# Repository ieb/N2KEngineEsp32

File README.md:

# NMEA 2000 Marine Diesel Engine Interface (ESP32-C3)

This project provides an open, high-reliability NMEA 2000 marine engine interface for diesel propulsion engines. Built on the **ESP32-C3** microcontroller and **ADS1115 16-bit ADCs**, it monitors engine speed, operating pressures, temperatures, electrical systems, and alarm conditions, broadcasting them across the vessel's NMEA 2000 CAN network.

---

## High-Level Architecture

```
                    +------------------------------------+
                    |             ESP32-C3               |
                    |                                    |
Flywheel Sensor --->| GPIO4 (Pulse Interrupt)            |
Stop Relay      --->| GPIO5 (Coil Sense)                 |
Glow Relay      --->| GPIO6 (Coil Sense)                 |
Start Relay     --->| GPIO7 (Coil Sense)                 |
1-Wire DS18B20  --->| GPIO0 (Dallas Temp Bus)            |
                    |                                    |
I2C Bus (SDA/SCL) ->| GPIO8 / GPIO9                      |
                    +-----+------------------------+-----+
                          |                        |
                          v                        v
             +-------------------------+     +------------+
             | 3x ADS1115 16-bit ADCs  |     | CAN / TWAI | (GPIO3 TX, GPIO1 RX)
             | (Running at 5V via LS)  |     +-----+------+
             +------------+------------+           |
                          |                        v
                          |                 +--------------+
  NTC1: Exhaust Water Trap|                 |  NMEA 2000   |
  NTC2: Alternator Temp   |                 |     Bus      |
  NTC3: Engine Room Temp  |                 +--------------+
  NTC4: Gearbox Temp      |
  NTC5: Exhaust Elbow Temp|
  Oil Pressure (0-5V)     |
  Coolant Sensor (12V)    |
  Engine Block Offset     |
  Engine Battery Voltage  |
  Alternator B+ Voltage   |
  Fuel Sender (0-190 ohm) |
```

---

## Key Hardware Peripherals & Pinout

| Pin | Peripheral | Purpose |
| :--- | :--- | :--- |
| **GPIO0** | 1-Wire | Dallas DS18B20 digital temperature bus (4K7 pull-up to 3V3) |
| **GPIO1** | CAN-RX | ESP32 TWAI CAN bus receive |
| **GPIO3** | CAN-TX | ESP32 TWAI CAN bus transmit |
| **GPIO2** | Bench Output | Optional LEDC test signal for RPM bench testing (CLI `T`) |
| **GPIO4** | Pulse Input | Flywheel reactive pickup via LM393 comparator (30 teeth per revolution) |
| **GPIO5** | Digital Input | Stop Relay Coil (10k / 4.7k divider from 12V, BAT46 clamp to 3V3) |
| **GPIO6** | Digital Input | Glow Plug Relay Coil (10k / 4.7k divider from 12V, BAT46 clamp to 3V3) |
| **GPIO7** | Digital Input | Start Relay Coil (10k / 4.7k divider from 12V, BAT46 clamp to 3V3) |
| **GPIO8** | I2C SDA | 400 kHz I2C data to 3x ADS1115 ADCs |
| **GPIO9** | I2C SCL | 400 kHz I2C clock to 3x ADS1115 ADCs |

### ADC Mapping (3x ADS1115 @ 5V, 64 SPS)
* **ADC1 (`0x48`, Addr $\to$ GND)**:
  * `AIN0`: NTC1 (10K NTC, 5V 4k7 pullup) — Exhaust Water Trap
  * `AIN1`: NTC2 (10K NTC, 5V 4k7 pullup) — Alternator Temperature
  * `AIN2`: NTC3 (10K NTC, 5V 4k7 pullup) — Engine Room Air Temperature
  * `AIN3`: Alternator Voltage Divider (10k / 4.7k)
* **ADC2 (`0x49`, Addr $\to$ VDD)**:
  * `AIN0`: Oil Pressure Sender (0–5V sensor)
  * `AIN1`: Engine Coolant Sensor (12V 1k pullup)
  * `AIN2`: Engine Block Negative Offset Divider (5V — 10k — ADC — 10k — Engine Block -)
  * `AIN3`: Engine Starting Battery Voltage Divider (10k / 4.7k)
* **ADC3 (`0x4B`, Addr $\to$ SCL)**:
  * `AIN0`: NTC4 (10K NTC, 5V 4k7 pullup) — Gearbox Temperature
  * `AIN1`: NTC5 (10K NTC, 5V 4k7 pullup) — Exhaust Elbow Temperature
  * `AIN2`: Fuel Tank Level Sender (European 0–190 $\Omega$, 5V 1k pullup)
  * `AIN3`: Spare Voltage Divider (10k / 4.7k)

---

## Signal Processing & Calibrations

1. **Engine Speed (RPM)**:
   * Computed from flywheel pulses: $\text{RPM} = \text{Hz} \times 2.0$.
   * Two implementations, selected with `RPM_SENSOR_EDGE_TIMING` in `src/config.h`:
     * **Edge timing** (`EdgeRpmSensor`, default): the ISR timestamps edges (1 µs) and RPM is computed over whole revolutions, giving a new value every revolution with accuracy limited only by interrupt latency jitter (~0.01–0.04%). Registered as an IRAM interrupt so pulses are not lost during flash writes; edges closer than 150 µs are rejected as glitches.
     * **Window counting** (`RpmSensor`): counts pulses over a ~100 ms window; ±1 pulse (±20 RPM) quantisation plus `millis()` jitter.
   * The ESP32-C3 has no PCNT (pulse counter) peripheral, so hardware counting is not available on this board.
   * The native tests print a side-by-side comparison of both implementations; on the board use the `T` bench signal.
   * Details, measurements and caveats: [docs/rpm_measurement.md](docs/rpm_measurement.md).
   * Engine is considered **Running** when $\text{RPM} \ge 800$ and **Stopping** when $\text{RPM} < 500$.
2. **10K NTC Thermistors (NTC1–NTC5)**:
   * Converted analytically using the exact Beta parameter model ($\frac{1}{T} = \frac{1}{T_0} + \frac{1}{\beta} \ln\left(\frac{R}{R_0}\right)$ with $R_0 = 10000\,\Omega$, $T_0 = 298.15\text{ K}$, $\beta = 3950\text{ K}$, $R_{\text{top}} = 4700\,\Omega$).
   * Provides smooth, continuous sub-0.01°C resolution matching the 16-bit ADS1115 without piecewise discretization or boundary kinks.
3. **Engine Block Negative Offset Compensation**:
   * Measures voltage drop between boat DC ground and engine block negative caused by heavy alternator charging current:
     $$V_{block} = 2.0 \cdot V_{adc} - 5.0\text{ V}$$
   * The Volvo Penta coolant sensor is connected to the engine block; its voltage reading and supply rail are automatically adjusted relative to $V_{block}$ to prevent false temperature spikes during high charging.
4. **Volvo Penta Coolant Temperature Sender**:
   * Evaluated through a dedicated lookup table (`coolantTable`, 10°C to 120°C) with ratiometric battery supply voltage compensation.
5. **Oil Pressure Sensor**:
   * Linear 0.5V (0 psi) to 4.5V (100 psi) transfer function with disconnection detection.
6. **Fuel Tank Level**:
   * Supports European 0–190 $\Omega$ resistive senders (0 $\Omega$ = Empty, 190 $\Omega$ = Full), scaled to 0.0%–100.0%.

---

## Alarms & Raw Water Flow Collapse Protection

* **15-Second Startup Grace Period**: Prevents spurious alarms while the engine spins up to idle.
* **Raw Water Flow Collapse Protection (Exhaust Elbow NTC5)**:
  * Evaluates rate-of-rise over a 30-second sliding anchor window. If exhaust elbow temperature climbs $\ge +8.0\text{°C}$ inside 30 seconds once above 35°C baseline, a raw water flow failure alarm is tripped immediately.
  * Absolute over-temperature alarm at $> 45.0\text{°C}$. If sustained for $> 5$ seconds, triggers an **Emergency Stop** discrete alarm.
* **Engine Protection Alarms**:
  * Coolant Over-Temperature: $> 97.0\text{°C}$ sustained $> 15$ seconds.
  * Low Oil Pressure: $< 10.0\text{ PSI}$ (68.9 kPa) sustained $> 5$ seconds while running.
  * Low System Voltage: Engine battery $< 11.8\text{ V}$ sustained $> 5$ seconds.
  * Alternator Charge Indicator: Alternator voltage $< 12.2\text{ V}$ sustained $> 5$ seconds.
  * High Alternator Temperature: Warning Level 1 triggered at $> 110.0\text{°C}$.
  * High Engine Room Temperature: Warning Level 1 triggered at $> 70.0\text{°C}$.

---

## Non-Volatile Storage & Event Logging

The flash memory uses a **2MB Application / 2MB SPIFFS** partition layout (`src/no_ota.csv`):
* **Engine Hours Accumulator**: Accumulated per second while $\text{RPM} \ge 800$, committed to wear-leveled NVS Preferences.
* **Persistent Event History**: Historical alarms are appended to `/events.csv` on the SPIFFS filesystem.
* **No flash writes while the engine runs**: flash writes stall non-IRAM interrupts (CAN today, BLE later) for up to tens of ms during a sector erase. While running, engine hours and alarm events are held in RTC no-init memory (survives crashes, watchdog resets and restarts) and written to flash when the stop relay is energised, when the engine stops and before a CLI restart. A valid RTC copy that is ahead of flash is recovered at boot. A backstop save of engine hours every `ENGINE_HOURS_BACKSTOP_SAVE_S` (default 3600 s, 0 disables) protects against an abnormal power cut; board power normally stays on 30–60 s after shutdown. Alarm flags are still sent immediately in PGN 127489. Setting hours (`E`) and clearing events (`C` / N2K command) write immediately.
* **GPS UTC Synchronization**: Automatically synchronizes timestamps when NMEA 2000 System Time (**PGN 126992**) is received from on-bus GPS receivers.

---

## NMEA 2000 Messages & Display Remapping

To allow standard marine multifunction displays (MFDs) and dedicated instruments (such as Raymarine i70) to present all engine and electrical metrics without proprietary software:

| PGN | Name | Period | Special Mapping / Rationale |
| :--- | :--- | :--- | :--- |
| **127488** | Engine Parameters, Rapid Update | 500 ms | RPM broadcast when engine is running ($\text{RPM} \ge 800$). |
| **127489** | Engine Parameters, Dynamic | 1000 ms | **Alternator Temp (NTC2)** sent as `Engine Oil Temperature` so standard gauges display alternator thermal load. Also conveys coolant temp, alternator voltage, total engine hours, oil pressure, and discrete alarm bitfields. |
| **127493** | Transmission Parameters, Dynamic | 4.85 s | **Exhaust Water Trap (NTC1)** sent as `Transmission Oil Temperature` for displays lacking an exhaust gauge. |
| **127508** | Battery Status | 1.0 s | Broadcasts two instances:<br>• **Instance 0**: Engine Starting Battery Voltage.<br>• **Instance 2**: Alternator Output Voltage & Operating Temperature. |
| **127505** | Fluid Level | 2.5 s | Tank Instance 0, Fuel level % (60.0 L capacity default). |
| **130312** | Temperature (Legacy) | 4.85 s | Emits Exhaust Gas (Source 14), Engine Room (Source 3), Alternator (Source 30), and Dallas 1-Wire sensors (Source 31+i). |
| **130316** | Extended Temperature | 2.5 s | Emits high-resolution (0.001 K) temperatures. |

---

## Interactive Serial Console

Connect to the USB Serial port at **115200 baud** for real-time monitoring and commands:

* `h` — Show command menu
* `s` — Print complete formatted engine status dashboard
* `F` — Toggle Fake 1000 RPM mode for bench testing
* `E` — Set / calibrate accumulated engine hours
* `l` — Dump SPIFFS alarm event log
* `C` — Clear SPIFFS event history
* `d` — Toggle raw ADC voltage debug stream
* `T` — Cycle the RPM bench test signal on GPIO2 (off → 100 Hz → 400 Hz → 1500 Hz) and print min/mean/max/std-dev of the measured RPM every 2 s. Wire GPIO2 → 1K → GPIO4 and short the flywheel input (J15) so the LM393 output is released. Build once with each `RPM_SENSOR_EDGE_TIMING` setting to compare.
* `R` — Software restart of the ESP32-C3

---

## Building & Flashing

This project uses [PlatformIO](https://platformio.org/):

```bash
# Build firmware
pio run

# Flash to ESP32-C3
pio run -t upload

# Open Serial Monitor
pio device monitor
```

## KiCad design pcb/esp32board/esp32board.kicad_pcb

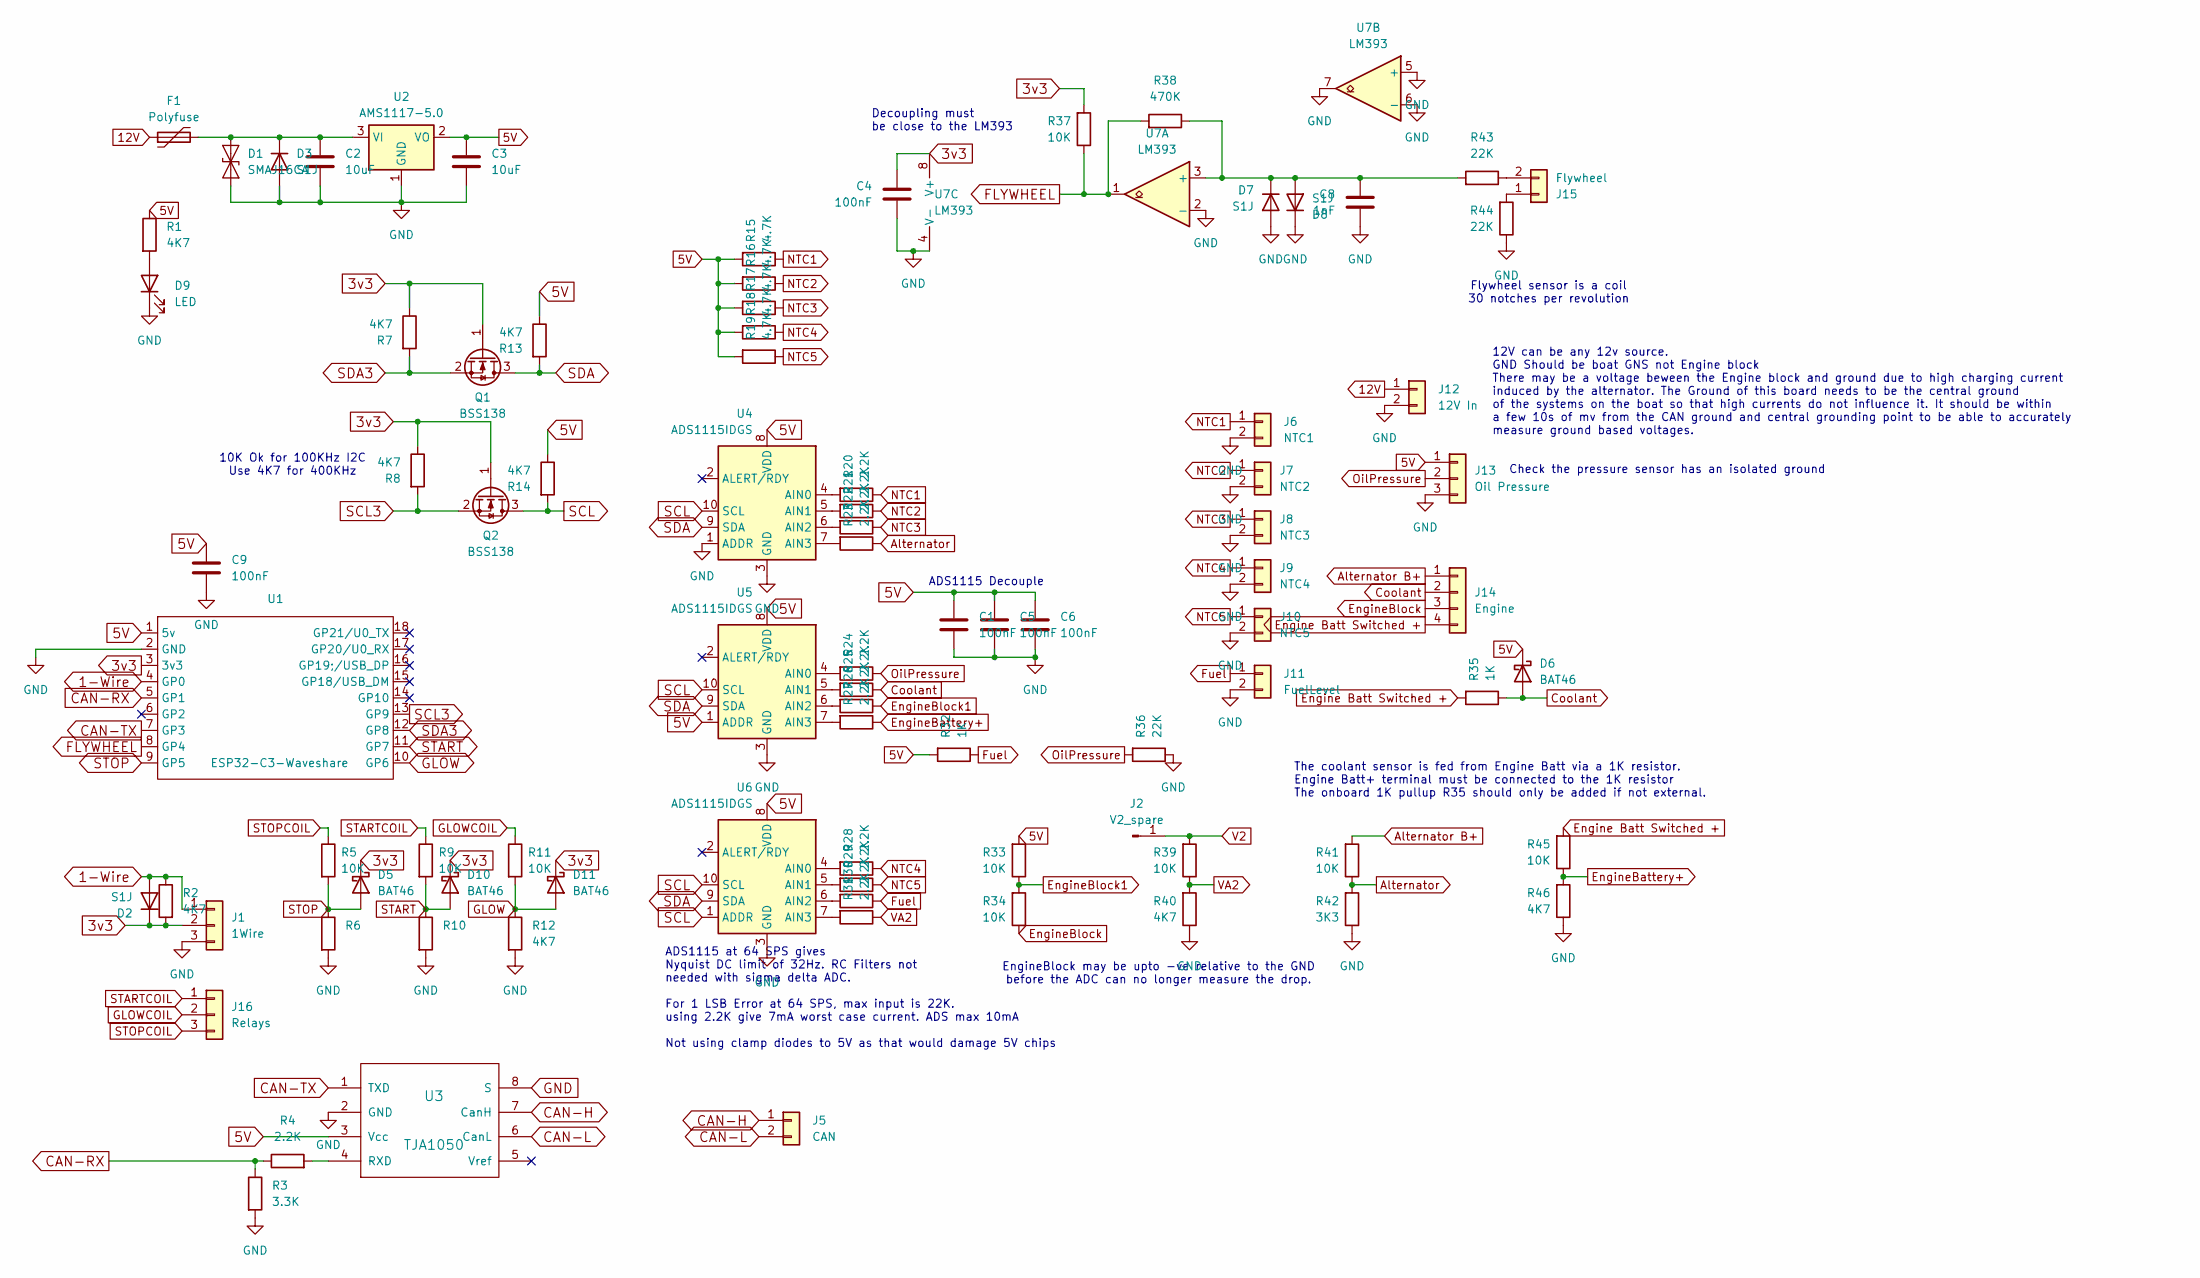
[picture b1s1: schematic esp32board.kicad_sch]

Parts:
C1, C4, C5, C6, C9: 100nF; C_0805_2012Metric_Pad1.18x1.45mm_HandSolder
C2, C3: 10uF; C_1206_3216Metric_Pad1.33x1.80mm_HandSolder
C8: 1nF; C_0805_2012Metric_Pad1.18x1.45mm_HandSolder
D1: SMAJ16CA; D_SMA-SMB_Universal_Handsoldering
D2, D3, D7, D8: S1J; D_SMA
D5, D6, D10, D11: BAT46; D_SOD-123
D9: LED; LED_0805_2012Metric_Pad1.15x1.40mm_HandSolder
F1: Polyfuse; Fuse_1812_4532Metric_Pad1.30x3.40mm_HandSolder
J1: 1Wire; JST_XH_B3B-XH-A_1x03_P2.50mm_Vertical
J2: V2_spare; PinHeader_1x01_P2.54mm_Vertical
J5: CAN; TerminalBlock_Phoenix_MKDS-1,5-2-5.08_1x02_P5.08mm_Horizont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
J6: NTC1; JST_XH_B2B-XH-A_1x02_P2.50mm_Vertical
J7: NTC2; JST_XH_B2B-XH-A_1x02_P2.50mm_Vertical
J8: NTC3; JST_XH_B2B-XH-A_1x02_P2.50mm_Vertical
J9: NTC4; JST_XH_B2B-XH-A_1x02_P2.50mm_Vertical
J10: NTC5; JST_XH_B2B-XH-A_1x02_P2.50mm_Vertical
J11: FuelLevel; JST_XH_B2B-XH-A_1x02_P2.50mm_Vertical
J12: 12V In; JST_XH_B2B-XH-A_1x02_P2.50mm_Vertical
J13: Oil Pressure; JST_XH_B3B-XH-A_1x03_P2.50mm_Vertical
J14: Engine; JST_XH_B4B-XH-A_1x04_P2.50mm_Vertical
J15: Flywheel; JST_XH_B2B-XH-A_1x02_P2.50mm_Vertical
J16: Relays; JST_XH_B3B-XH-A_1x03_P2.50mm_Vertical
Q1, Q2: BSS138; SOT-23
R1, R2, R6, R7, R8, R10, R12, R13, R14, R40, R46: 4K7; R_0805_2012Metric_Pad1.20x1.40mm_HandSolder
R3: 3.3K; R_0805_2012Metric_Pad1.20x1.40mm_HandSolder
R4, R20, R21, R22, R23, R24, R25, R26, R27, R28, R29, R30, R31: 2.2K; R_0805_2012Metric_Pad1.20x1.40mm_HandSolder
R5, R9, R11, R33, R34, R37, R39, R41, R45: 10K; R_0805_2012Metric_Pad1.20x1.40mm_HandSolder
R15, R16, R17, R18, R19: 4.7K; R_0805_2012Metric_Pad1.20x1.40mm_HandSolder
R32: 1K; R_0805_2012Metric_Pad1.20x1.40mm_HandSolder
R35: 1K; R_Axial_DIN0204_L3.6mm_D1.6mm_P5.08mm_Horizontal
R36, R43, R44: 22K; R_0805_2012Metric_Pad1.20x1.40mm_HandSolder
R38: 470K; R_0805_2012Metric_Pad1.20x1.40mm_HandSolder
R42: 3K3; R_0805_2012Metric_Pad1.20x1.40mm_HandSolder
U1: ESP32-C3-Waveshare; ESP-C3-Zero-Waveshare
U2: AMS1117-5.0; SOT-223-3_TabPin2
U3: TJA1050; SOIC-8_3.9x4.9mm_P1.27mm
U4, U5, U6: ADS1115IDGS; TSSOP-10_3x3mm_P0.5mm
U7: LM393; SOIC-8_3.9x4.9mm_P1.27mm

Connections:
1-Wire: D2.2 (A), J1.1, R2.1, U1.4 (GP0)
3v3: C4.2, D2.1 (K), D5.1 (K), D10.1 (K), D11.1 (K), J1.2, Q1.1 (G), Q2.1 (G), R2.2, R7.1, R8.1, R37.2, U1.3 (3v3), U7.8 (V+)
5V: C1.1, C3.1, C5.1, C6.1, C9.1, D6.1 (K), J13.1, R1.1, R13.1, R14.1, R15.2, R16.2, R17.2, R18.2, R19.2, R32.2, R33.2, U1.1 (5v), U2.2 (VO), U3.3 (Vcc), U4.8 (VDD), U5.1 (ADDR), U5.8 (VDD), U6.8 (VDD)
12V: F1.1, J12.1
Alternator: R23.1, R41.1, R42.2
Alternator B+: J14.1, R41.2
CAN-H: J5.1, U3.7 (CanH)
CAN-L: J5.2, U3.6 (CanL)
CAN-RX: R3.1, R4.1, U1.5 (GP1)
CAN-TX: U1.7 (GP3), U3.1 (TXD)
Coolant: D6.2 (A), J14.2, R25.1, R35.1
Engine Batt Switched +: J14.4, R35.2, R45.2
EngineBattery+: R27.1, R45.1, R46.2
EngineBlock: J14.3, R34.1
EngineBlock1: R26.1, R33.1, R34.2
FLYWHEEL: R37.1, R38.2, U1.8 (GP4), U7.1
Fuel: J11.1, R30.1, R32.1
GLOW: D11.2 (A), R11.2, R12.1, U1.10 (GP6)
GLOWCOIL: J16.2, R11.1
GND: C1.2, C2.2, C3.2, C4.1, C5.2, C6.2, C8.1, C9.2, D1.1 (A1), D3.2 (A), D7.2 (A), D8.1 (K), D9.1 (K), J1.3, J6.2, J7.2, J8.2, J9.2, J10.2, J11.2, J12.2, J13.3, R3.2, R6.2, R10.2, R12.2, R36.1, R40.1, R42.1, R44.1, R46.1, U1.2 (GND), U2.1 (GND), U3.2 (GND), U3.8 (S), U4.1 (ADDR), U4.3 (GND), U5.3 (GND), U6.3 (GND), U7.2 (-), U7.4 (V-), U7.5 (+), U7.6 (-), U7.7
NTC1: J6.1, R15.1, R20.1
NTC2: J7.1, R16.1, R21.1
NTC3: J8.1, R17.1, R22.1
NTC4: J9.1, R18.1, R28.1
NTC5: J10.1, R19.1, R29.1
unnamed: C2.1, D1.2 (A2), D3.1 (K), F1.2, U2.3 (VI)
unnamed: C8.2, D7.1 (K), D8.2 (A), R38.1, R43.2, U7.3 (+)
unnamed: D9.2 (A), R1.2
unnamed: J15.1, R44.2
unnamed: J15.2, R43.1
unnamed: R4.2, U3.4 (RXD)
unnamed: R20.2, U4.4 (AIN0)
unnamed: R21.2, U4.5 (AIN1)
unnamed: R22.2, U4.6 (AIN2)
unnamed: R23.2, U4.7 (AIN3)
unnamed: R24.2, U5.4 (AIN0)
unnamed: R25.2, U5.5 (AIN1)
unnamed: R26.2, U5.6 (AIN2)
unnamed: R27.2, U5.7 (AIN3)
unnamed: R28.2, U6.4 (AIN0)
unnamed: R29.2, U6.5 (AIN1)
unnamed: R30.2, U6.6 (AIN2)
unnamed: R31.2, U6.7 (AIN3)
OilPressure: J13.2, R24.1, R36.2
SCL: Q2.3 (D), R14.2, U4.10 (SCL), U5.10 (SCL), U6.1 (ADDR), U6.10 (SCL)
SCL3: Q2.2 (S), R8.2, U1.13 (GP9)
SDA: Q1.3 (D), R13.2, U4.9 (SDA), U5.9 (SDA), U6.9 (SDA)
SDA3: Q1.2 (S), R7.2, U1.12 (GP8)
START: D10.2 (A), R9.2, R10.1, U1.11 (GP7)
STARTCOIL: J16.1, R9.1
STOP: D5.2 (A), R5.2, R6.1, U1.9 (GP5)
STOPCOIL: J16.3, R5.1
V2: J2.1, R39.2
VA2: R31.1, R39.1, R40.2

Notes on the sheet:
ADS1115 at 64 SPS gives Nyquist DC limit of 32Hz. RC Filters not needed with sigma delta ADC. For 1 LSB Error at 64 SPS, max input is 22K. using 2.2K give 7mA worst case current. ADS max 10mA Not using clamp diodes to 5V as that would damage 5V chips
ADS1115 Decouple
Flywheel sensor is a coil 30 notches per revolution
Decoupling must be close to the LM393
EngineBlock may be upto -ve relative to the GND before the ADC can no longer measure the drop.
10K Ok for 100KHz I2C Use 4K7 for 400KHz
The coolant sensor is fed from Engine Batt via a 1K resistor. Engine Batt+ terminal must be connected to the 1K resistor The onboard 1K pullup R35 should only be added if not external.
Check the pressure sensor has an isolated ground
12V can be any 12v source. GND Should be boat GNS not Engine block There may be a voltage beween the Engine block and ground due to high charging current induced by the alternator. The Ground of this board needs to be the central ground of the systems on the boat so that high currents do not influe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

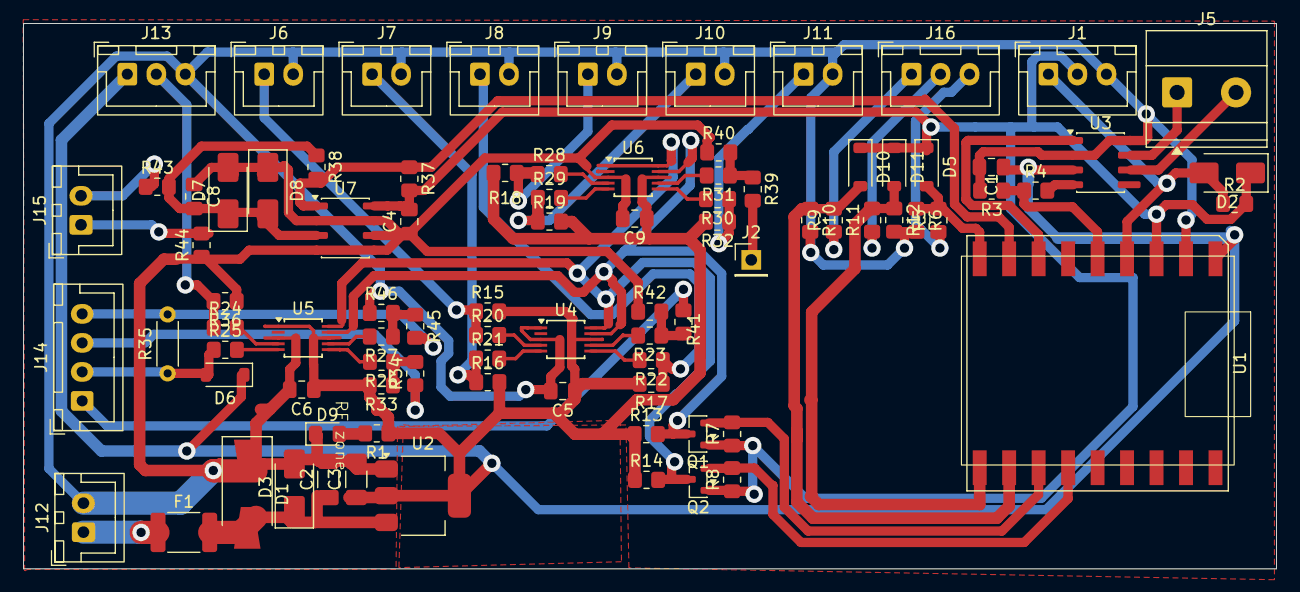
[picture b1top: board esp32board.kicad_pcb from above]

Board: 2 copper layers, 108.0 x 47.0 mm, 88 parts (0 on the bottom side), 54 nets.

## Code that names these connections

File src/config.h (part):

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// ============================================================================
#define PIN_CAN_RX          1
#define PIN_CAN_TX          3
#define PIN_FLYWHEEL        4
#define PIN_STOP_COIL       5
#define PIN_GLOW_COIL       6
#define PIN_START_COIL      7
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#define I2C_FREQUENCY       400000UL

// ADS1115 I2C Addresses (7-bit)
#define ADS1115_ADDR_1      0x48   // Addr pin -> GND: NTC1, NTC2, NTC3, Alternator Voltage
#define ADS1115_ADDR_2      0x49   // Addr pin -> VDD: Oil Press, Coolant, Engine Block, Engine Battery
#define ADS1115_ADDR_3      0x4B   // Addr pin -> SCL: NTC4, NTC5, Fuel, Spare Voltage

// ADS1115 SPS (64 SPS gives DC Nyquist 32Hz, matches sigma-delta filtering)
#define ADS1115_SPS         64
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#define RPM_EDGE_PARTIAL_TIMEOUT_US 250000UL

// Bench test signal (LEDC square wave). Wire GPIO2 -> 1K -> GPIO4 and short the
// flywheel input (J15) so the LM393 output is released. GPIO2 is a strapping pin;
// the 10K pull-up on GPIO4 keeps it high at boot as required.
#define PIN_BENCH_SIGNAL            2
#define BENCH_LEDC_CHANNEL          0
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#define FUEL_TANK_INSTANCE          0

// Temperature sources / instances (PGN 130312 / 130316)
#define TEMP_INSTANCE_EXHAUST_TRAP  0      // NTC1, Source 14 (Exhaust Gas)
#define TEMP_INSTANCE_EXHAUST_ELBOW 1      // NTC5, Source 14 (Exhaust Gas)
#define TEMP_SOURCE_ALTERNATOR      30     // NTC2
#define TEMP_SOURCE_ONEWIRE_BASE    31     // 1-Wire sensor i -> 31 + i (i = 0..3)
#define TEMP_SOURCE_GEARBOX         35     // NTC4

// Proprietary PGNs
#define PROPRIETARY_CODE            0x9FFE // Manufacturer 2046 + Marine bit
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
